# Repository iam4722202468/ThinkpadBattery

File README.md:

# ThinkpadBattery
Open source Thinkpad battery design

## What is this?

This is a fully open source laptop battery design. The design uses an attiny85, which can reply to the T420 motherboard's SMBUS requests.

## Setup

### Configurable Constants

- BATTERY_CAPACITY | Your battery capacity in mAH
- V_HIGH | The highest output voltage of your battery, normally 12.6v
- V_LOW | The cutoff for when the battery will stop working, normally around 10.8v

### Creating your own

Parts Needed
- Arduino Uno/Mega  (for programming the attiny85, Mega needs different pin assignment)
- 12v Lithium-Ion battery pack
- 3S Lithium-Ion BMS (it might be possible to use the existing bms if specification is available but communication needs to be implemented)
- Components from schematic
- PCB from schematic

Once you have all these parts, assemble the pcb and attach a BMS to your battery pack. Solder the 12v battery output/input to the large pads on the pcb, then program the attiny85 with the included ino file. The output pins at the bottom of the PCB are a 1-1 mapping of the motherboard pin input.

### Debugging

- The laptop won't supply power to the board unless it detects there's a battery attached, meaning if you plug the board in to the battery without having an external battery to power it, it won't work.

### Libraries

Use the ATTinyCore for compiling. Without it, Wire.h won't work.

## Limitations

### Voltage Reading / Remaining battery

Currently remaining battery %'s aren't exact because I'm assuming there is a linear coorelation between voltage and capacity (Which is wrong). This is probably fixable using a battery gas gauge, I'll have to investiage more.

### MCU Power Consumption

By design, the MCU will always be on as long as a battery is connected to it. This can cause the battery to slowly run out of power if it isn't connected to a laptop. A potential fix could be to implement a low power mode for the attiny, or have a seperate disconnect switch for the battery power on the battery pack itself.

### 3D Printable Case for T420 only

The case for the cells has been completed. The case model and stl files are included in /model

## Future Plans

iam4722202468 - Design and manufacture a PCB with current,voltage and battery capacity measuring capabilities, an easily programmable microcontroller, and a 3s balanced charger

pj1976 - Find a bms that would fit, or try to talk with bq29312pw that was in the original pack

## Credits

iam4722202468 - Initial work, T420 9 cell model

pj1976 - Added support for R50

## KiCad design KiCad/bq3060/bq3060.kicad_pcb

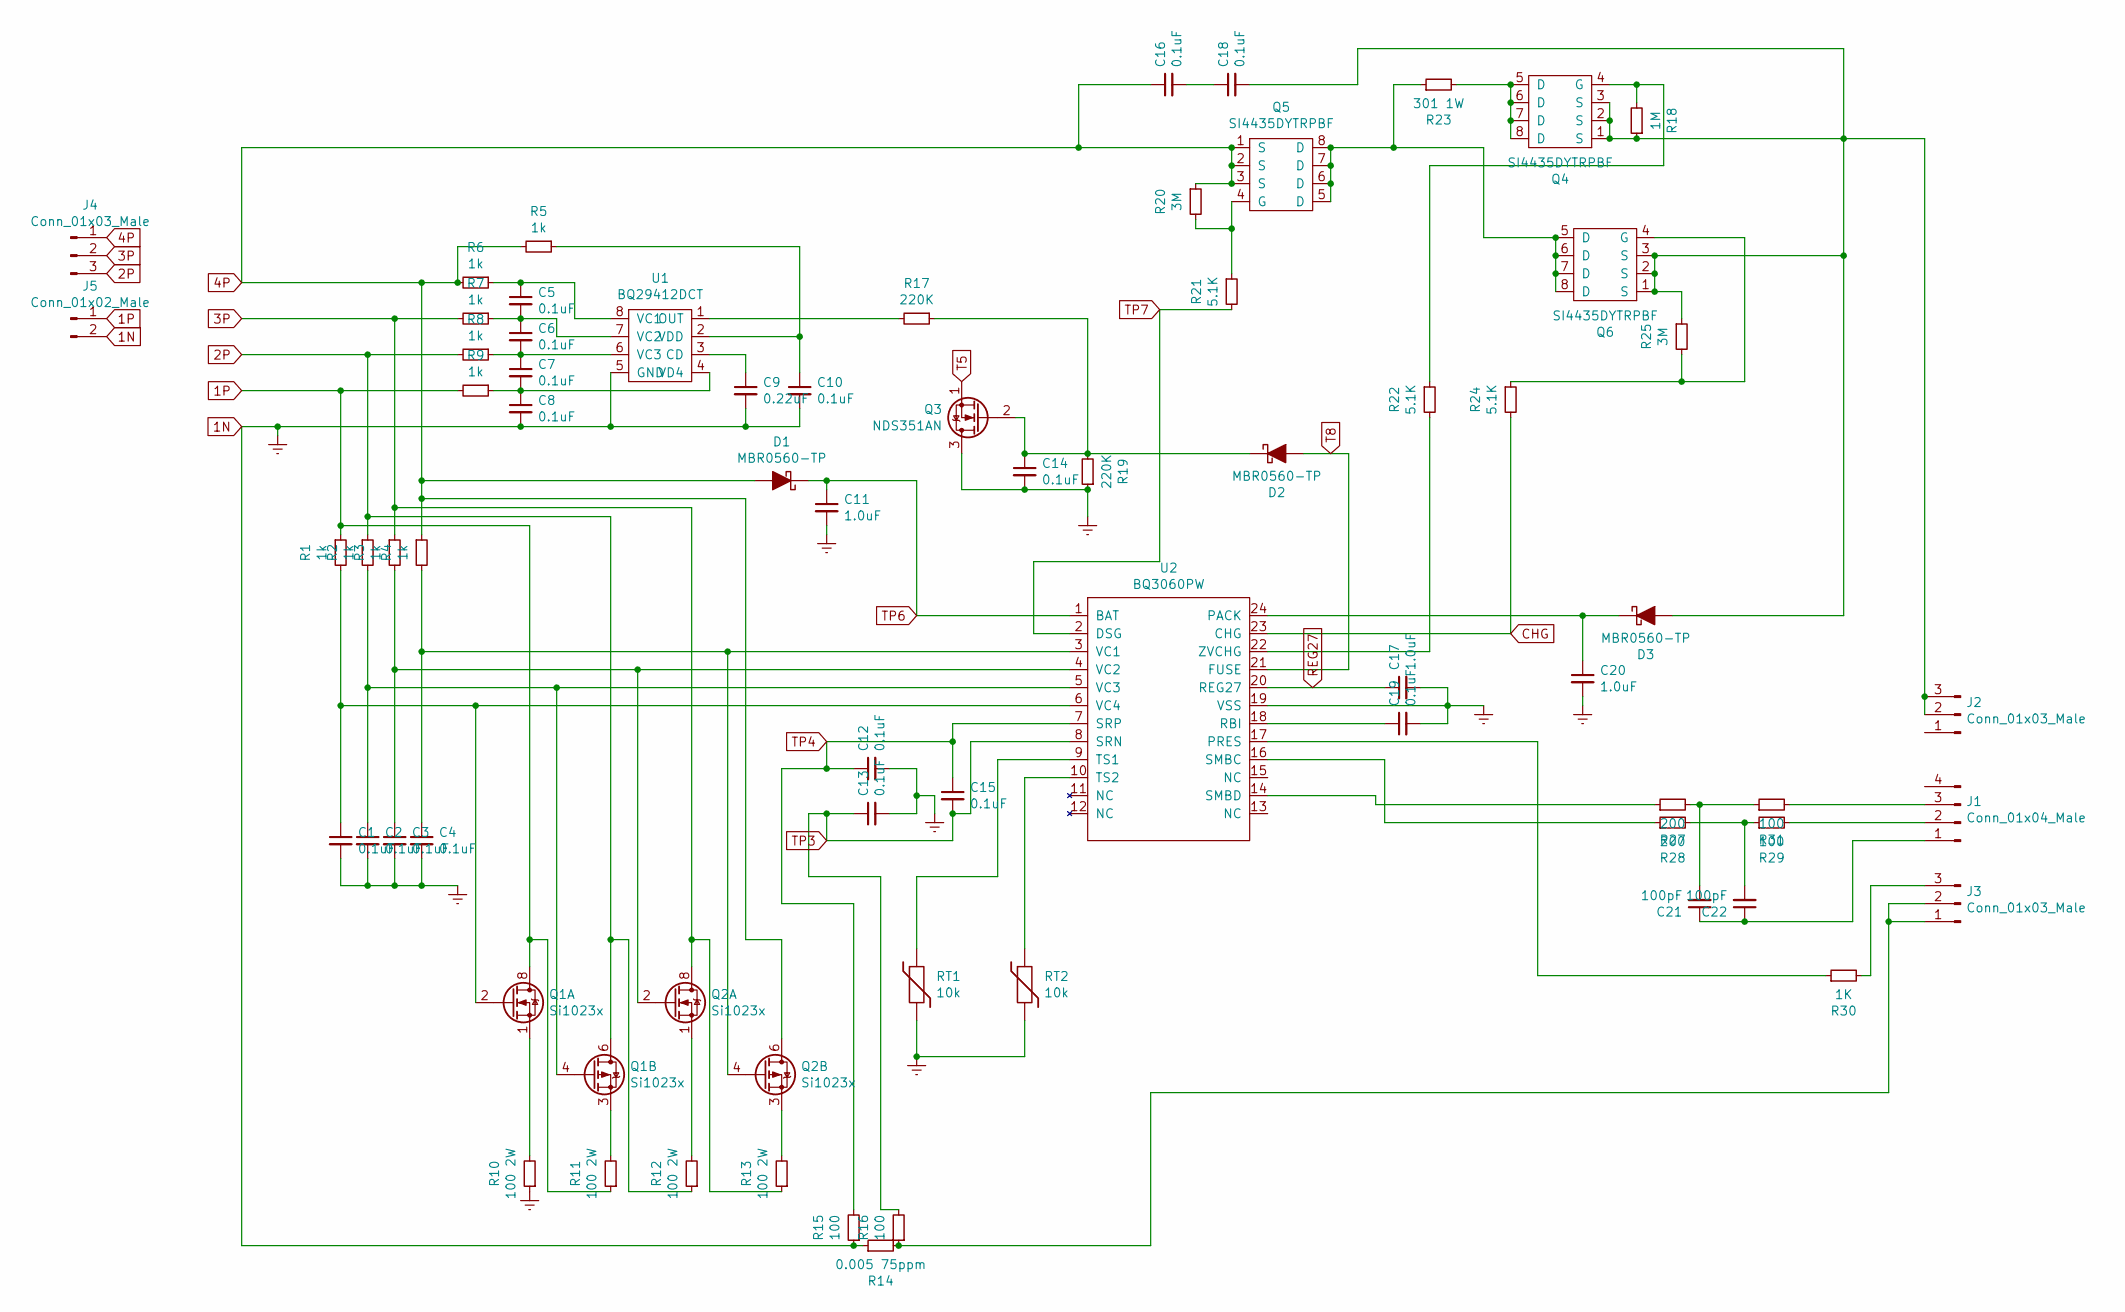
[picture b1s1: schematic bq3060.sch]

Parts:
C1, C2, C3, C4, C5, C6, C7, C8, C10, C12, C13, C14, C15, C16, C18, C19: 0.1uF; C_0805_2012Metric_Pad1.15x1.40mm_HandSolder
C9: 0.22uF; C_0805_2012Metric_Pad1.15x1.40mm_HandSolder
C11, C17, C20: 1.0uF; C_0805_2012Metric_Pad1.15x1.40mm_HandSolder
C21, C22: 100pF; C_0805_2012Metric_Pad1.15x1.40mm_HandSolder
D1, D2, D3: MBR0560-TP; D_SOD-123
J1: Conn_01x04_Male; PinHeader_1x04_P2.54mm_Horizontal
J2, J3: Conn_01x03_Male; PinHeader_1x03_P2.54mm_Vertical
J4: Conn_01x03_Male; SolderWirePad_1x03_P5.715mm_Drill2mm
J5: Conn_01x02_Male; SolderWirePad_1x02_P7.62mm_Drill2mm
Q1, Q2: Si1023x; SOIC-8_3.9x4.9mm_P1.27mm
Q3: NDS351AN; SOT-23
Q4, Q5, Q6: SI4435DYTRPBF; SOIC-8_3.9x4.9mm_P1.27mm
R1, R2, R3, R4, R5, R6, R7, R8, R9: 1k; R_0805_2012Metric_Pad1.15x1.40mm_HandSolder
R10, R11, R12, R13: 100 2W; R_2512_6332Metric_Pad1.52x3.35mm_HandSolder
R14: 0.005 75ppm; R_2512_6332Metric_Pad1.52x3.35mm_HandSolder
R15, R16, R29, R31: 100; R_0805_2012Metric_Pad1.15x1.40mm_HandSolder
R17, R19: 220K; R_0805_2012Metric_Pad1.15x1.40mm_HandSolder
R18: 1M; R_0805_2012Metric_Pad1.15x1.40mm_HandSolder
R20, R25: 3M; R_0805_2012Metric_Pad1.15x1.40mm_HandSolder
R21, R22, R24: 5.1K; R_0805_2012Metric_Pad1.15x1.40mm_HandSolder
R23: 301 1W; R_2512_6332Metric_Pad1.52x3.35mm_HandSolder
R27, R28: 200; R_0805_2012Metric_Pad1.15x1.40mm_HandSolder
R30: 1K; R_0805_2012Metric_Pad1.15x1.40mm_HandSolder
RT1, RT2: 10k; R_0805_2012Metric_Pad1.15x1.40mm_HandSolder
U1: BQ29412DCT; SN74LVC2G241_DCT_8
U2: BQ3060PW; TSSOP-24_4.4x7.8mm_P0.65mm

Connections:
1N: C1.2, C2.2, C3.2, C4.2, C8.2, C9.2, C10.2, C11.2, C12.2, C13.2, C14.2, C17.2, C19.2, C20.2, J5.2, Q3.3 (D), R10.1, R14.1, R15.1, R19.1, RT1.2, RT2.2, U1.5 (GND), U2.19 (VSS)
1P: J5.1, Q1.7 (D), Q1.8 (D), R1.1, R9.2, R11.1
2P: J4.3, Q1.5 (D), Q1.6 (D), R2.1, R8.2, R12.1
3P: J4.2, Q2.7 (D), Q2.8 (D), R3.1, R7.2, R13.1
4P: C16.1, D1.2 (A), J4.1, Q2.5 (D), Q2.6 (D), Q5.1 (S), Q5.2 (S), Q5.3 (S), R4.1, R5.2, R6.2, R20.1
CHG: R24.2, U2.23 (CHG)
unnamed: C1.1, Q1.2 (G), R1.2, U2.6 (VC4)
unnamed: C2.1, Q1.4 (G), R2.2, U2.5 (VC3)
unnamed: C3.1, Q2.2 (G), R3.2, U2.4 (VC2)
unnamed: C4.1, Q2.4 (G), R4.2, U2.3 (VC1)
unnamed: C5.1, R6.1, U1.8 (VC1)
unnamed: C5.2, C6.1, R7.1, U1.7 (VC2)
unnamed: C6.2, C7.1, R8.1, U1.6 (VC3)
unnamed: C7.2, C8.1, R9.1, U1.4 (VD4)
unnamed: C9.1, U1.3 (CD)
unnamed: C10.1, R5.1, U1.2 (VDD)
unnamed: C14.1, D2.1 (K), Q3.2 (G), R17.1, R19.2
unnamed: C16.2, C18.1
unnamed: C18.2, D3.2 (A), J2.2, J2.3, Q4.1 (S), Q4.2 (S), Q4.3 (S), Q6.1 (S), Q6.2 (S), Q6.3 (S), R18.1, R25.1
unnamed: C19.1, U2.18 (RBI)
unnamed: C20.1, D3.1 (K), U2.24 (PACK)
unnamed: C21.1, C22.1, J1.1
unnamed: C21.2, R27.2, R31.1
unnamed: C22.2, R28.2, R29.1
unnamed: J1.2, R29.2
unnamed: J1.3, R31.2
unnamed: J3.1, J3.2, R14.2, R16.1
unnamed: J3.3, R30.2
unnamed: Q1.1 (S), R10.2
unnamed: Q1.3 (1), R11.2
unnamed: Q2.1 (S), R12.2
unnamed: Q2.3 (1), R13.2
unnamed: Q4.4 (G), R18.2, R22.1
unnamed: Q4.5 (D), Q4.6 (D), Q4.7 (D), Q4.8 (D), R23.2
unnamed: Q5.4 (G), R20.2, R21.1
unnamed: Q5.5 (D), Q5.6 (D), Q5.7 (D), Q5.8 (D), Q6.5 (D), Q6.6 (D), Q6.7 (D), Q6.8 (D), R23.1
unnamed: Q6.4 (G), R24.1, R25.2
unnamed: R17.2, U1.1 (OUT)
unnamed: R22.2, U2.22 (ZVCHG)
unnamed: R27.1, U2.14 (SMBD)
unnamed: R28.1, U2.16 (SMBC)
unnamed: R30.1, U2.17 (PRES)
unnamed: RT1.1, U2.9 (TS1)
unnamed: RT2.1, U2.10 (TS2)
REG27: C17.1, U2.20 (REG27)
T5: Q3.1 (S)
T8: D2.2 (A), U2.21 (FUSE)
TP3: C13.1, C15.2, R16.2, U2.8 (SRN)
TP4: C12.1, C15.1, R15.2, U2.7 (SRP)
TP6: C11.1, D1.1 (K), U2.1 (BAT)
TP7: R21.2, U2.2 (DSG)

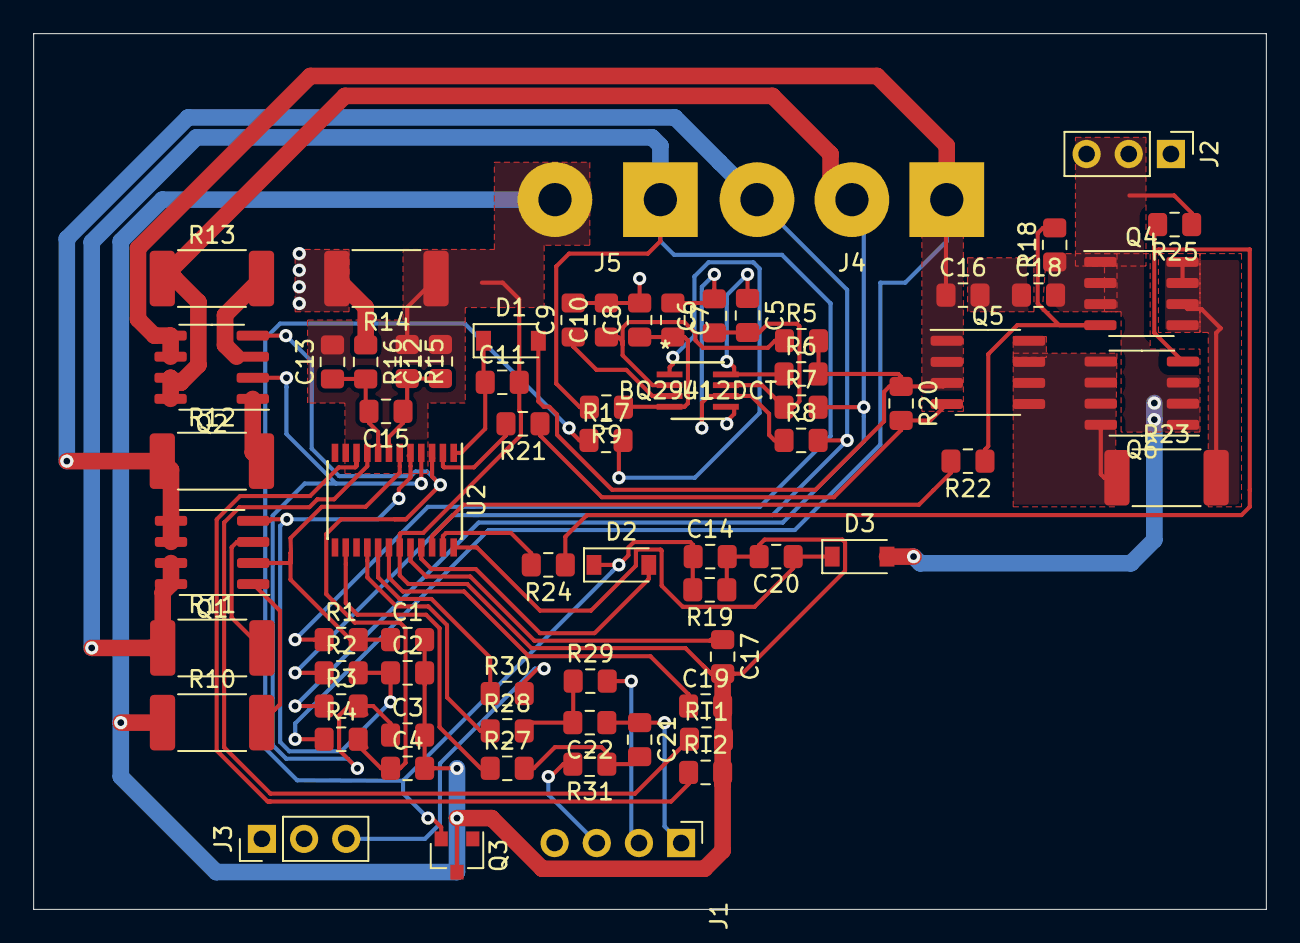
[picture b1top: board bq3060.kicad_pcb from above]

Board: 2 copper layers, 74.2 x 52.8 mm, 70 parts (0 on the bottom side), 50 nets.

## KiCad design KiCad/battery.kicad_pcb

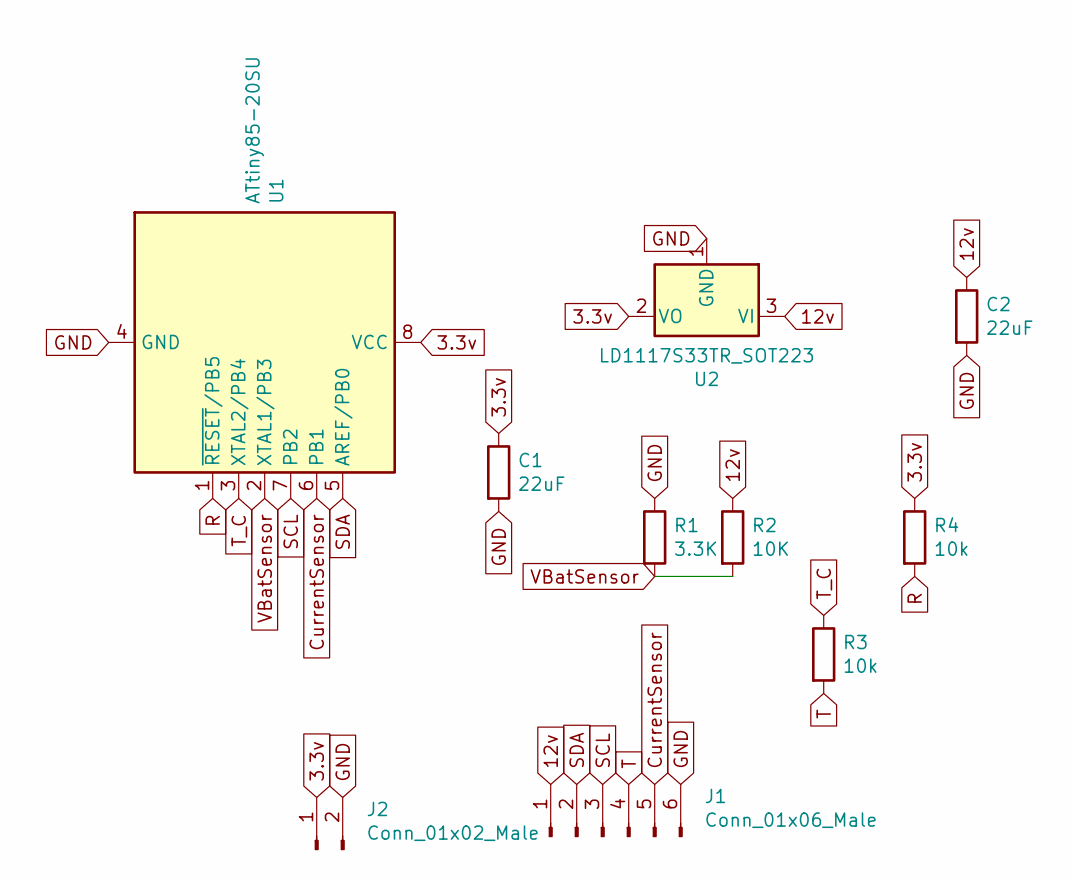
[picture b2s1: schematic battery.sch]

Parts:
C1, C2: 22uF; C_0805_2012Metric
J1: Conn_01x06_Male; PinHeader_1x06_P2.54mm_Horizontal
J2: Conn_01x02_Male; PinHeader_1x02_P2.54mm_Vertical
R1: 3.3K; R_0402_1005Metric
R2: 10K; R_0402_1005Metric
R3, R4: 10k; R_0402_1005Metric
U1: ATtiny85-20SU; SOIJ-8_5.3x5.3mm_P1.27mm
U2: LD1117S33TR_SOT223; SOT-223-3_TabPin2

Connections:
3.3v: C1.1, J2.1, R4.1, U1.8 (VCC), U2.2 (VO)
12v: C2.1, J1.1, R2.1, U2.3 (VI)
CurrentSensor: J1.5, U1.6 (PB1)
GND: C1.2, C2.2, J1.6, J2.2, R1.1, U1.4 (GND), U2.1 (GND)
R: R4.2, U1.1 (~RESET~/PB5)
SCL: J1.3, U1.7 (PB2)
SDA: J1.2, U1.5 (AREF/PB0)
T: J1.4, R3.2
T_C: R3.1, U1.3 (XTAL2/PB4)
VBatSensor: R1.2, R2.2, U1.2 (XTAL1/PB3)

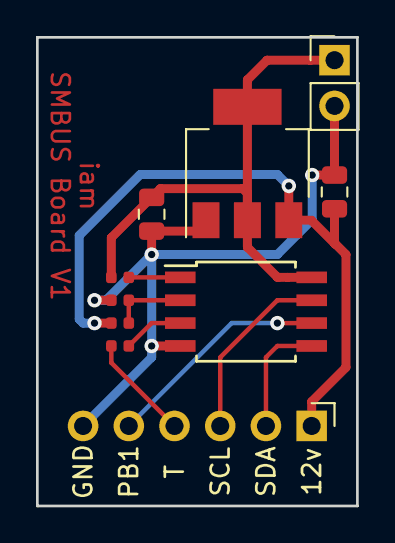
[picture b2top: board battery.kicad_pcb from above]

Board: 2 copper layers, 17.8 x 26.0 mm, 10 parts (0 on the bottom side), 10 nets.

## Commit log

2020-08-27 Add gitignore
2020-08-27 Fix readme
2020-08-28 Use PB4 to pull T pin low instead of PB5
2020-08-28 Remove old code
2020-08-31 Add 3d model of case
2020-09-01 Add locking mechanism to case model
2020-09-01 Modify locking mechanism to work better
2020-09-03 Create LICENSE
2020-09-03 Work on making latching mechansim spring back
2020-09-04 Improve battery model
2020-09-06 better pcb
2020-09-12 Redesign latch mechanism
2020-09-27 Finalize designs
2020-09-29 Finish model
2020-09-29 Add stl files
2020-09-29 Smooth out edges
2020-09-29 Split up flat surfaces
2020-09-30 Decrease voltage limit low
2020-09-30 Make battery 162wh
2020-10-02 Add comment to code
2020-10-02 Add comment
2020-10-04 Glitch T pin for charging
2020-10-05 Revert changes
2020-10-10 Update PCB before manufacturing
2021-04-25 Update batteryEmulator.ino
    R50 support
2021-04-26 Update README.md
    Fix formatting
2021-05-21 R1 bq3060
2021-05-21 Finish bq3060 schematic
2021-05-22 Routing attempt
2021-06-22 Tried routing again
2021-07-23 Comment batteryEmulator.ino
2021-07-23 Add prototype bq3060 design
2022-04-30 Handle case where SMBus command is not implemented
    NULL is returned from the function map for not-yet-implemented commands. Previously this would result in attempting to call `0()`, which is invalid. This change instead simply skips unimplemented com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
    See https://onlinegdb.com/BZmJknxpB for a minimal working example.
2022-05-08 Lowercase hex codes for better readability
    `18` and `1B` are ambiguous in many fonts, including GitHub's.
2022-05-08 Order callbacks by hex value and mark missing
    This lines the functions up with the documentation the reader is consulting, which makes the code easier to navigate.
    It also adds comments to mark where the missing callbacks should go.
    I realize this is a massive lineno change; feel free to copy-paste into your own commit.

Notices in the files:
parts and their libraries:
Copyright 2016 Accelerated Designs. All rights reserved.
